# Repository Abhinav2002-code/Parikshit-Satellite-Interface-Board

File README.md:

# PA Interface Board

This is the Interface board for performance  
assurance of the Parikshit Student Satellite.

## About the project

The Parikshit Student satellite is a team of 25 undergraduates skilled in building nanosatellites.  
This PCB is a card used as an interface between  
the testing jigs in the teams lab and the nanosatellite system.

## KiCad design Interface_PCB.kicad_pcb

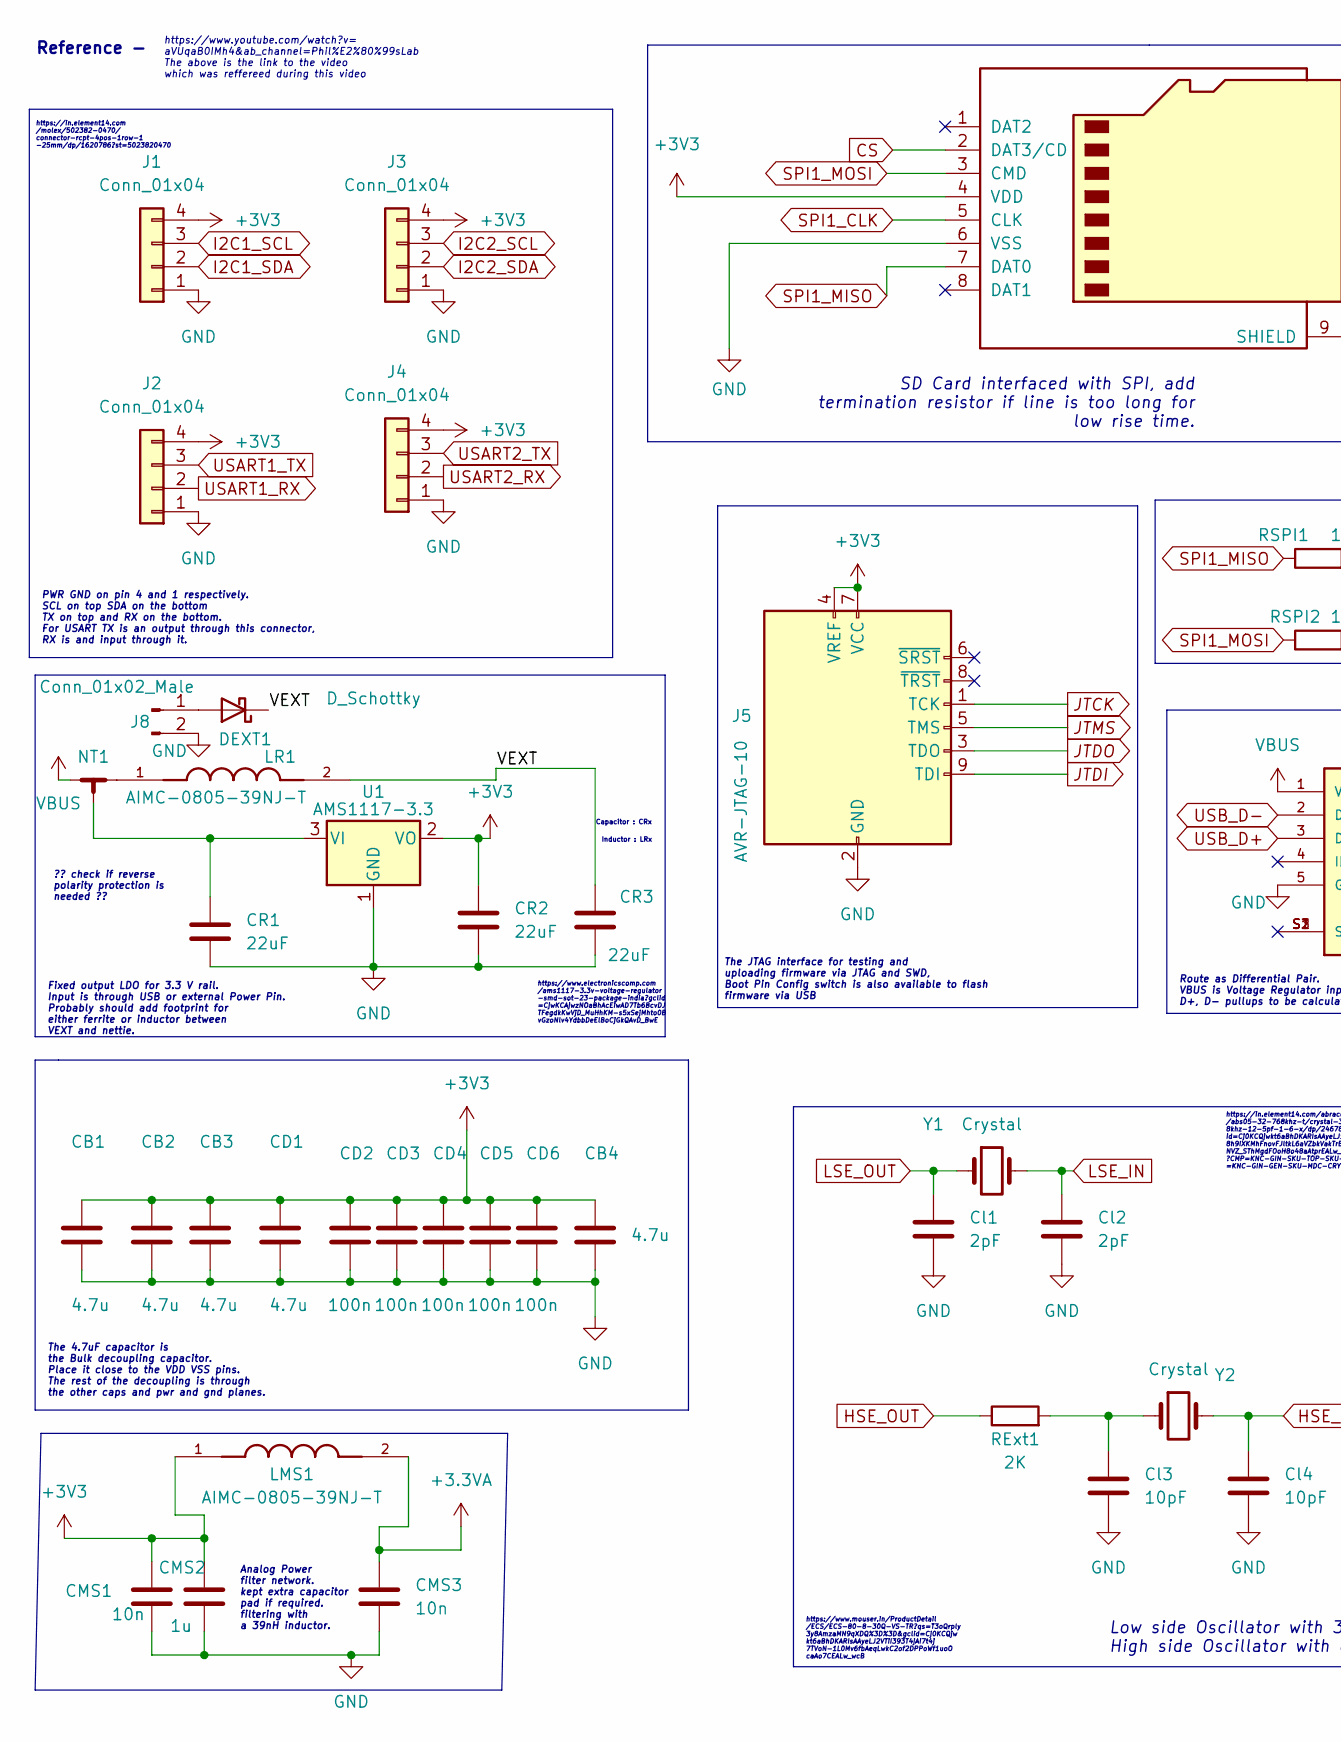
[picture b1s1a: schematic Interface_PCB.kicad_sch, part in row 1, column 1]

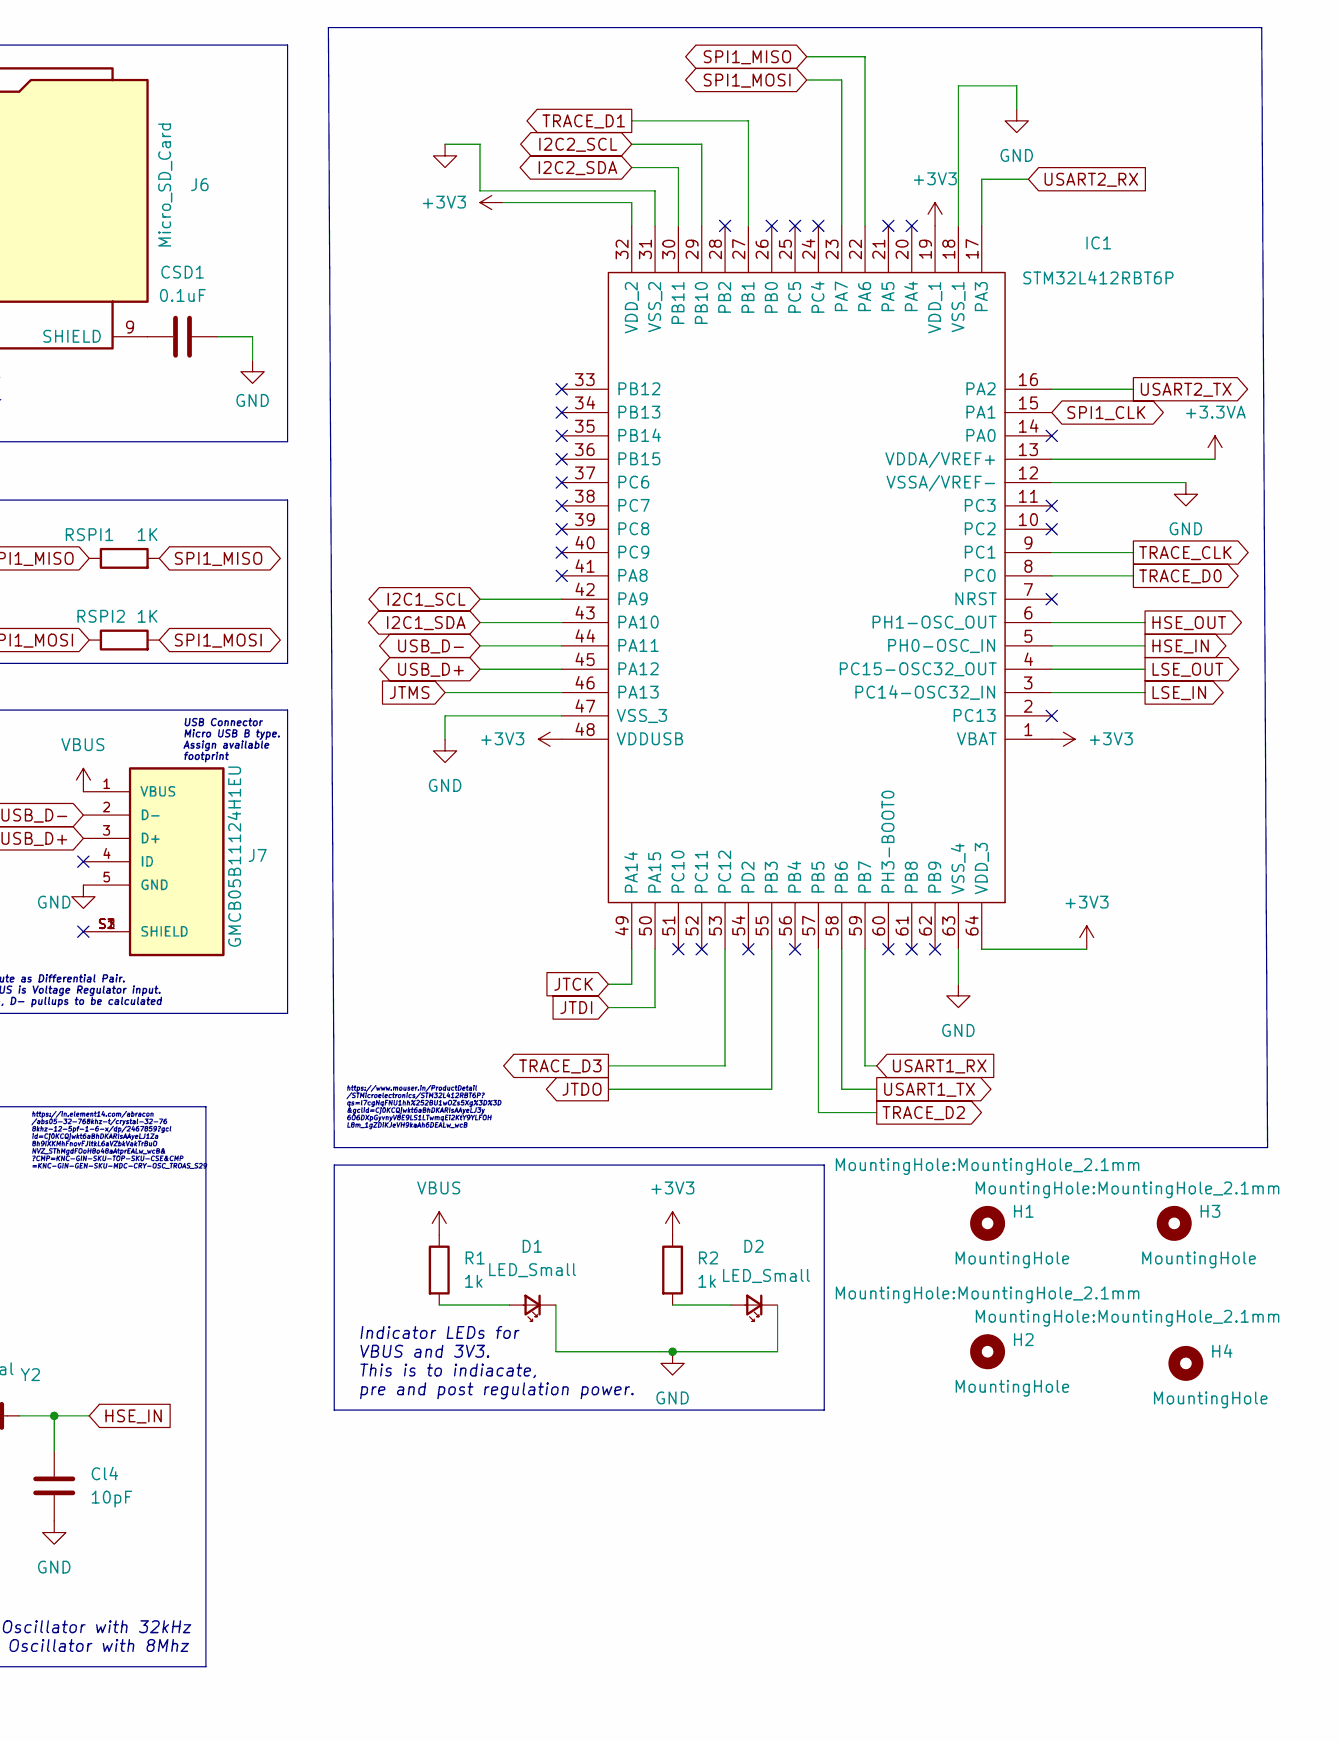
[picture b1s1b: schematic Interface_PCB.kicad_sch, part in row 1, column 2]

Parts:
CB1, CB2, CB3, CB4: 4.7u; C_0805_2012Metric
CD1: 4.7u; C_0402_1005Metric
CD2, CD3, CD4, CD5, CD6: 100n; C_0402_1005Metric
CMS1, CMS3: 10n; C_0805_2012Metric
CMS2: 1u; C_0805_2012Metric
CR1, CR2, CR3: 22uF; C_0402_1005Metric
CSD1: 0.1uF; C_0402_1005Metric
Cl1, Cl2: 2pF; C_0402_1005Metric
Cl3, Cl4: 10pF; C_0402_1005Metric
D1, D2: LED_Small; LED_0805_2012Metric
DEXT1: D_Schottky; AQ120501ETG
H1, H2, H3, H4: MountingHole; MountingHole_2.1mm
IC1: STM32L412RBT6P; QFP50P1200X1200X160-64N; Mouser Part Number 511-STM32L412RBT6P
J1, J2, J3, J4: Conn_01x04; 502382-0470
J5: AVR-JTAG-10; FTSH10501LDVK
J6: Micro_SD_Card; 693072010801
J7: GMCB05B11124H1EU; AMPHENOL_GMCB05B11124H1EU; PARTREV C
J8: Conn_01x02_Male; PinHeader_1x02_P2.54mm_Vertical
LMS1: AIMC-0805-39NJ-T; INDC2012X105N
LR1: AIMC-0805-39NJ-T; INDC2012X105N
NT1: NetTie_3_Tee; NetTie-3_SMD_Pad2.0mm
R1, R2: 1k; R_0805_2012Metric
RExt1: 2K; R_0603_1608Metric
RSPI1, RSPI2: 1K; R_0402_1005Metric
U1: AMS1117-3.3; SOT-223-3_TabPin2
Y1: Crystal; ABS05W32768KHZD2T
Y2: Crystal; ECS80830QVSTR

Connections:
+3.3VA: CMS3.1, IC1.13 (VDDA/VREF+), LMS1.2
+3V3: CB1.1, CB2.1, CB3.1, CB4.1, CD1.1, CD2.1, CD3.1, CD4.1, CD5.1, CD6.1, CMS1.1, CMS2.1, CR2.1, IC1.1 (VBAT), IC1.19 (VDD_1), IC1.32 (VDD_2), IC1.48 (VDDUSB), IC1.64 (VDD_3), J1.4, J2.4, J3.4, J4.4, J5.4 (VREF), J5.7 (VCC), J6.4 (VDD), LMS1.1, R2.1, U1.2 (VO)
/VEXT: CR3.1, DEXT1.1 (K), LR1.2
CS: J6.2 (DAT3/CD)
GND: CB1.2, CB2.2, CB3.2, CB4.2, CD1.2, CD2.2, CD3.2, CD4.2, CD5.2, CD6.2, CMS1.2, CMS2.2, CMS3.2, CR1.2, CR2.2, CR3.2, CSD1.2, Cl1.2, Cl2.2, Cl3.2, Cl4.2, D1.1 (K), D2.1 (K), IC1.12 (VSSA/VREF-), IC1.18 (VSS_1), IC1.31 (VSS_2), IC1.47 (VSS_3), IC1.63 (VSS_4), J1.1, J2.1, J3.1, J4.1, J5.2 (GND), J5.10 (GND), J6.6 (VSS), J7.5 (GND), J8.2, U1.1 (GND)
HSE_IN: Cl4.1, IC1.5 (PH0-OSC_IN), Y2.2
HSE_OUT: IC1.6 (PH1-OSC_OUT), RExt1.1
I2C1_SCL: IC1.42 (PA9), J1.3
I2C1_SDA: IC1.43 (PA10), J1.2
I2C2_SCL: IC1.29 (PB10), J3.3
I2C2_SDA: IC1.30 (PB11), J3.2
JTCK: IC1.49 (PA14), J5.1 (TCK)
JTDI: IC1.50 (PA15), J5.9 (TDI)
JTDO: IC1.55 (PB3), J5.3 (TDO)
JTMS: IC1.46 (PA13), J5.5 (TMS)
LSE_IN: Cl2.1, IC1.3 (PC14-OSC32_IN), Y1.2
LSE_OUT: Cl1.1, IC1.4 (PC15-OSC32_OUT), Y1.1
unnamed: CR1.1, NT1.3, U1.3 (VI)
unnamed: CSD1.1, J6.9 (SHIELD)
unnamed: Cl3.1, RExt1.2, Y2.1
unnamed: D1.2 (A), R1.2
unnamed: D2.2 (A), R2.2
unnamed: DEXT1.2 (A), J8.1
unnamed: LR1.1, NT1.2
SPI1_CLK: IC1.15 (PA1), J6.5 (CLK)
SPI1_MISO: IC1.22 (PA6), J6.7 (DAT0), RSPI1.1, RSPI1.2
SPI1_MOSI: IC1.23 (PA7), J6.3 (CMD), RSPI2.1, RSPI2.2
TRACE_CLK: IC1.9 (PC1)
TRACE_D0: IC1.8 (PC0)
TRACE_D1: IC1.27 (PB1)
TRACE_D2: IC1.57 (PB5)
TRACE_D3: IC1.53 (PC12)
USART1_RX: IC1.59 (PB7), J2.2
USART1_TX: IC1.58 (PB6), J2.3
USART2_RX: IC1.17 (PA3), J4.2
USART2_TX: IC1.16 (PA2), J4.3
USB_D+: IC1.45 (PA12), J7.3 (D+)
USB_D-: IC1.44 (PA11), J7.2 (D-)
VBUS: J7.1 (VBUS), NT1.1, R1.1

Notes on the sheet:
Fixed output LDO for 3.3 V rail. Input is through USB or external Power Pin. Probably should add footprint for either ferrite or inductor between VEXT and nettie.
USB Connector Micro USB B type. Assign available footprint
The JTAG interface for testing and uploading firmware via JTAG and SWD, Boot Pin Config switch is also available to flash firmware via USB
Capacitor : CRx
SD Card interfaced with SPI, add termination resistor if line is too long for low rise time.
?? check if reverse polarity protection is needed ??
Reference -
Indicator LEDs for VBUS and 3V3. This is to indiacate, pre and post regulation power.
https://www.mouser.in/ProductDetail /STMicroelectronics/STM32L412RBT6P? qs=l7cgNqFNU1hh%252BU1wOZs5Xg%3D%3D &gclid=Cj0KCQjwkt6aBhDKARIsAAyeLJ3y 6O6DXpGyvnyV8E9LS1LTwmqEi2KtY9YLFOH L8m_1gZDiKJeVH9kaAh6DEALw_wcB
https://in.element14.com/abracon /abs05-32-768khz-t/crystal-32-76 8khz-12-5pf-1-6-x/dp/2467859?gcl id=Cj0KCQjwkt6aBhDKARIsAAyeLJ1Za 8h9IXKMhFnovFJltkL6aVZbkVakTrBuO NVZ_SThMgdFOoH8o48aAtprEALw_wcB& ?CMP=KNC-GIN-SKU-TOP-SKU-CSE&CMP =KNC-GIN-GEN-SKU-MDC-CRY-OSC_TROAS_S29
https://www.youtube.com/watch?v= aVUqaB0IMh4&ab_channel=Phil%E2%80%99sLab The above is the link to the video which was reffereed during this video
Analog Power filter network. kept extra capacitor pad if required. filtering with a 39nH inductor.
Low side Oscillator with 32kHz High side Oscillator with 8Mhz
Route as Differential Pair. VBUS is Voltage Regulator input. D+, D- pullups to be calculated
https://www.mouser.in/ProductDetail /ECS/ECS-80-8-30Q-VS-TR?qs=T3oQrply 3y8AmzaMN9qXDQ%3D%3D&gclid=Cj0KCQjw kt6aBhDKARIsAAyeLJ2VTiI393T4jAi7t4j 7TVoN-1L0Mv6fbAeqLwkC2of2DPPoWf1uoO caAo7CEALw_wcB
https://www.electronicscomp.com /ams1117-3.3v-voltage-regulator -smd-sot-23-package-india?gclid =CjwKCAjwzNOaBhAcEiwAD7Tb6BcvDJ TFegdkKwVjD_MuHhKM-s5xSejMhto0B vGzoNlv4YdbbDeElBoCjGkQAvD_BwE
https://in.element14.com /molex/502382-0470/ connector-rcpt-4pos-1row-1 -25mm/dp/1620786?st=5023820470
Inductor : LRx
PWR GND on pin 4 and 1 respectively. SCL on top SDA on the bottom TX on top and RX on the bottom. For USART TX is an output through this connector, RX is and input through it.
The 4.7uF capacitor is the Bulk decoupling capacitor. Place it close to the VDD VSS pins. The rest of the decoupling is through the other caps and pwr and gnd planes.

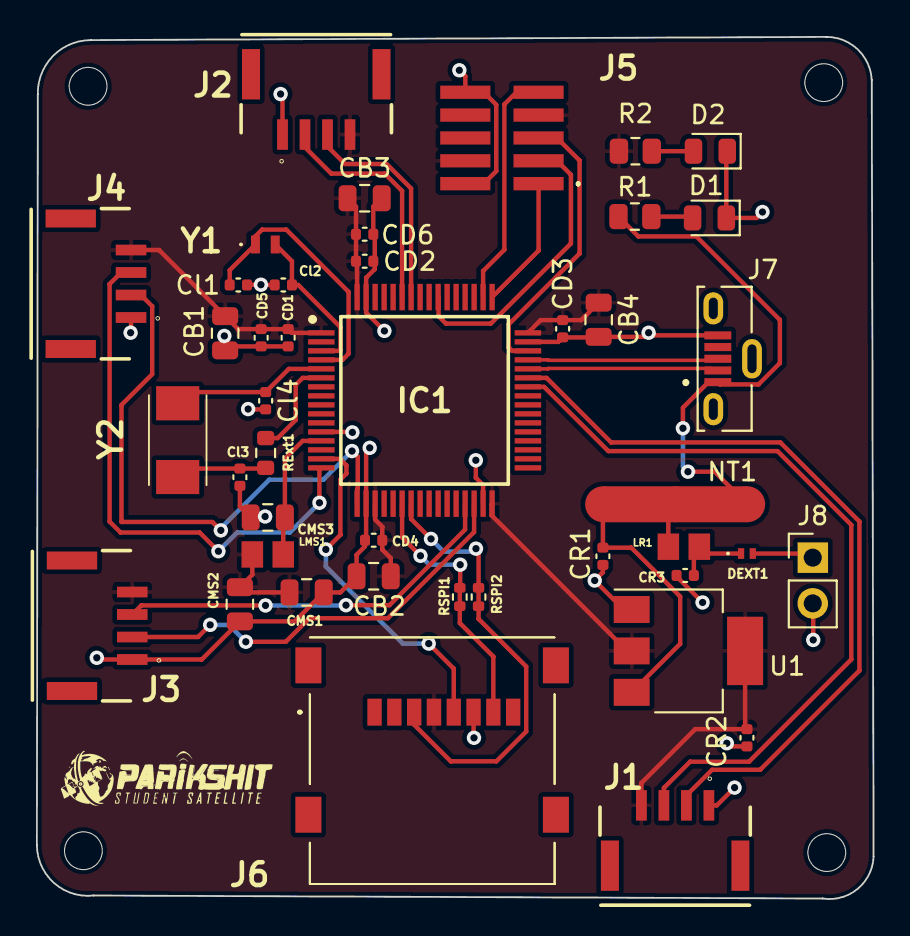
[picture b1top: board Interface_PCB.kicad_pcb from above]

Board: 2 copper layers, 46.5 x 47.9 mm, 47 parts (0 on the bottom side), 32 nets.

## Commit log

2022-10-02 Interface Board Schematic
2022-10-03 Indicator LEDs added and AMS1117 added but not connected
2022-10-03 AMS connected
2022-10-03 Added crystal configs to schematic
2022-10-04 OSC design corrected
2022-10-04 Full Schematic Rev 1.0
2022-10-04 Final Schematic done, footprint assignment TBD
2022-10-04 Components are on PCB doc, Stackup and Layout to be done, verify footprints
2022-10-23 Caps and inductors annotated properly, regulator changed to fixed regulator, resource links added
2022-10-25 README added
2022-10-25 Added all component links and modified the footprints
2022-10-28 Layout Revision 1
2022-10-28 Layout rev 1.1
2022-10-29 Footprint zip files added
2022-10-29 Layout rev2.0
2022-11-02 Layout rev3.0 - redesigned
2022-11-04 Design rev4.0
2022-11-04 got rid of gnd parasitic vias around USB diff pair
2022-11-04 Edge cuts are improved
2022-11-04 Design rev 4.1
2022-11-04 Resistor pads to SD card connector
2022-11-04 Added BOM, position and gerber files
2022-11-05 Added TVS diode and External Voltage (BOM and gerber included)
2022-11-06 Corrected the annotations
2022-11-06 Added Full BOM and gerber
2022-11-06 Oscillators are brought closer
2022-11-06 Design 5.0
2022-12-08 Updated inductor and USB according to manufacturer
